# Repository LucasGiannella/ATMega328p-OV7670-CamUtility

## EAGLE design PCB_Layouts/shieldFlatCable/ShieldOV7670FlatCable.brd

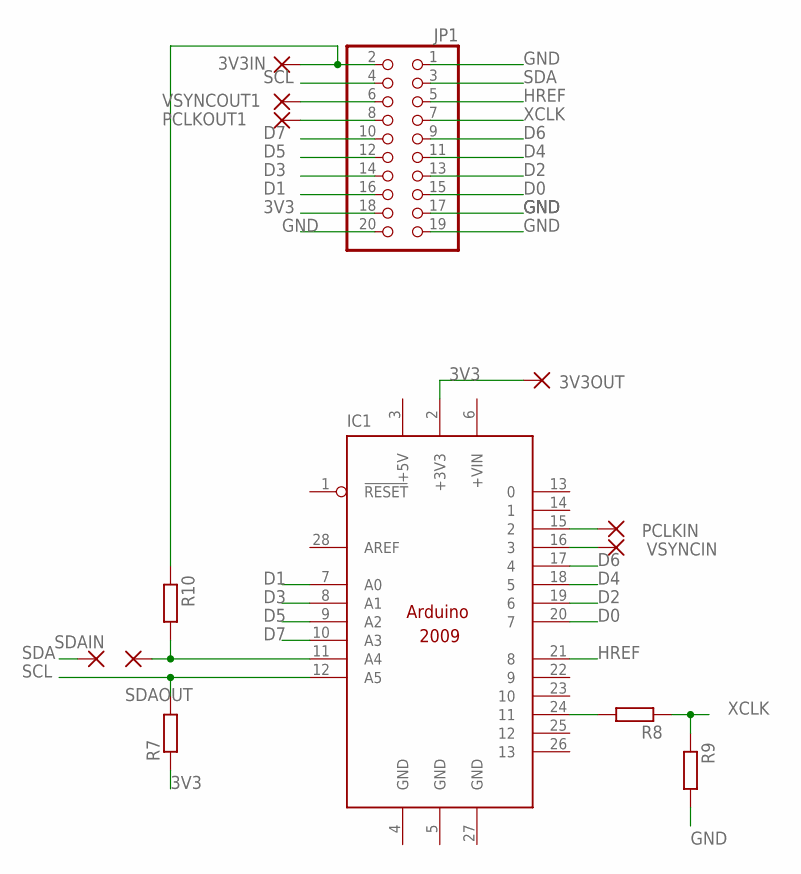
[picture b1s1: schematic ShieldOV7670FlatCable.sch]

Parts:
3V3IN, 3V3OUT: 1,6/0,9
IC1: ARDUINO2009_12; ARDUINO2009_2
JP1: PINHD-2X10; 2X10
PCLKIN: 1,6/0,9
PCLKOUT1: 1,6/0,9
R7, R8, R9, R10: R-EU_0207/12; 0207/12
SDAIN: 1,6/0,9
SDAOUT: 1,6/0,9
VSYNCIN: 1,6/0,9
VSYNCOUT1: 1,6/0,9

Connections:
3V3: 3V3OUT.1, IC1.2 (+3V3), JP1.18, R7.1
+5V: IC1.3 (+5V)
D0: IC1.20 (7), JP1.15
D1: IC1.7 (A0), JP1.16
D2: IC1.19 (6), JP1.13
D3: IC1.8 (A1), JP1.14
D4: IC1.18 (5), JP1.11
D5: IC1.9 (A2), JP1.12
D6: IC1.17 (4), JP1.9
D7: IC1.10 (A3), JP1.10
GND: IC1.4 (GND), IC1.5 (GND), IC1.27 (GND), JP1.1, JP1.17, JP1.19, JP1.20, R9.2
HREF: IC1.21 (8), JP1.5
unnamed: IC1.15 (2), PCLKIN.1
unnamed: IC1.16 (3), VSYNCIN.1
unnamed: 3V3IN.1, JP1.2, R10.1
unnamed: IC1.11 (A4), R10.2, SDAOUT.1
unnamed: IC1.24 (11), R8.2
unnamed: JP1.6, VSYNCOUT1.1
unnamed: JP1.8, PCLKOUT1.1
SCL: IC1.12 (A5), JP1.4, R7.2
SDA: JP1.3, SDAIN.1
XCLK: JP1.7, R8.1, R9.1

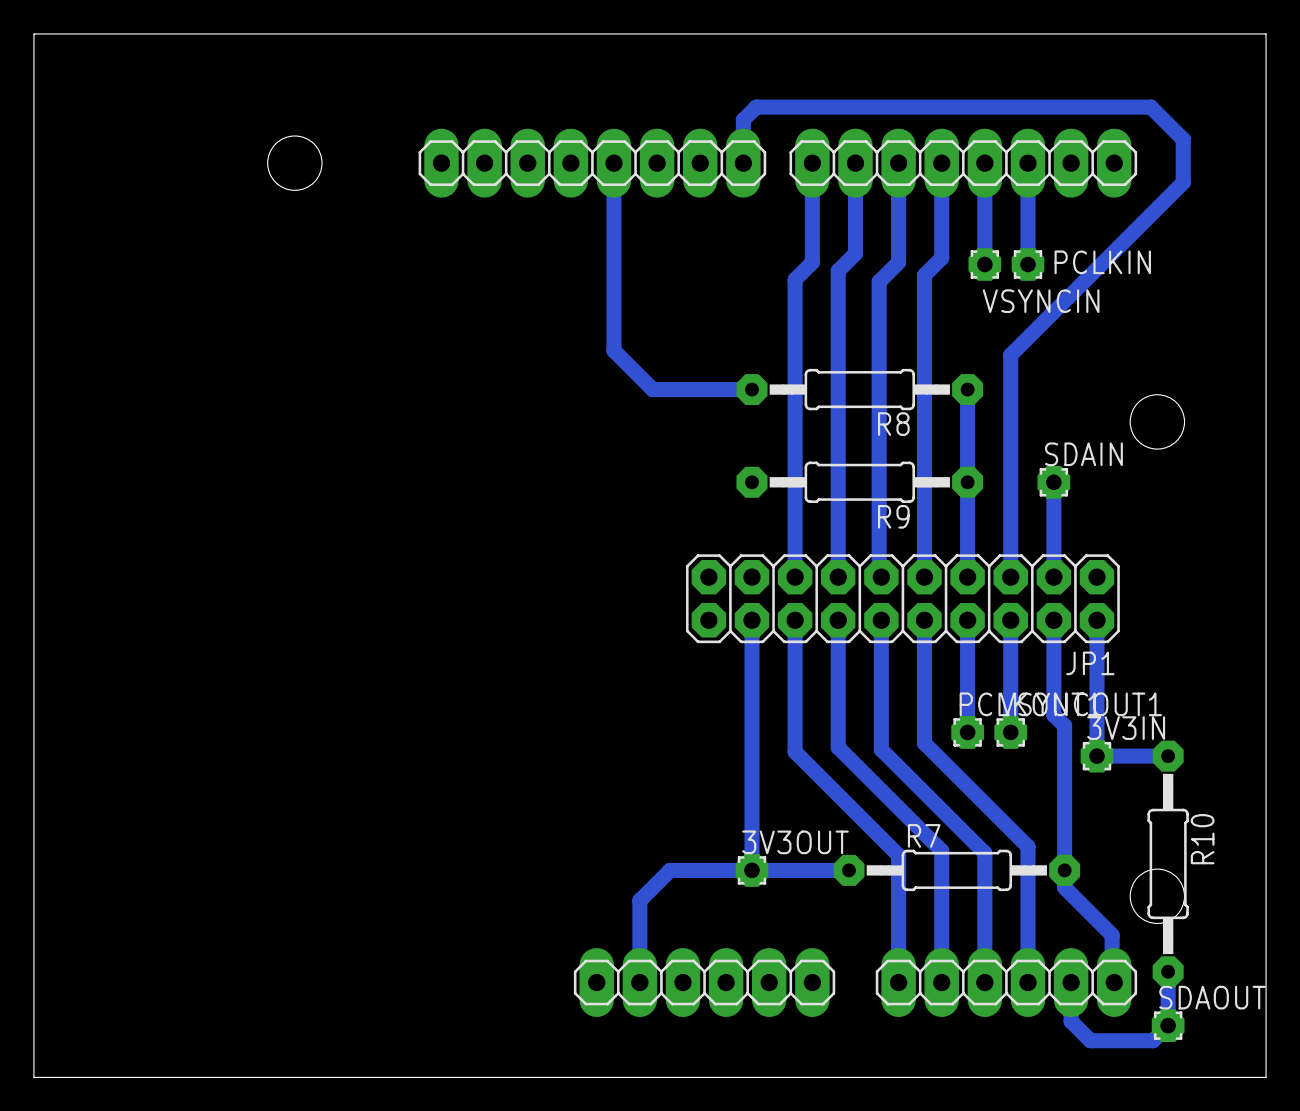
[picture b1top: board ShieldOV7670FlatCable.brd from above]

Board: 2 copper layers, 72.6 x 61.5 mm, 14 parts (0 on the bottom side), 21 nets.

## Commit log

2019-12-10 Added doc folder and pdf files
2019-12-10 Use defined values for pins Output/Input Description Added code for XCLK set
    Issues: Evaluate XCLK clock boudaries, eletrical conditions
2019-12-10 Corrected issues related to XCLK clock. Should expect clock frequencies of 8MHz on pin PB3
2019-12-10 Corrected PORT definitions and directions for GPIO usage
2019-12-10 Corrected USART Speed Configuration
2019-12-12 Added Python & Matlab files for more testing
2019-12-18 Cleaned main defines and add RGB image capture
2019-12-18 add OV7670 initial codes
2019-12-18 Changed "\n" on the img capture fucntion to 0x10 (LF)
2019-12-18 Tested some possibilitys for the image composing VS Russian shot
2019-12-18 Saved matrixes for comparision
2019-12-20 Added folder w/ MATLAB img reconstruction tests
2019-12-22 Changed the serial read method seems to be the correct way now
2019-12-25 Merry X-mas; tested taking a shot w/ low light enviroment -> BW bal err
2019-12-25 Tried main.cpp w/ frameGrabber unsuccessfully @ \ov7670\2019_12_25
2019-12-25 Add sequence shot script; The BW balance changes when arduino reset
2020-01-02 Tested Auto White Balance Adjust time it takes about 12s
2020-01-21 Tested and failed arduino's input position change -> manipulation prob
2020-01-29 Corrected bit output for PCB Shield adpting
2020-02-04 Add layout folder w/ flatcable adapter shield for arduino uno
2020-02-04 Added final arduino code for shield using @ 2020/02/03
2020-02-06 Clened some archives tested capturing w/out setting delays
2020-03-01 Lots of days working, shield doesnt work, color test is strange, sad
